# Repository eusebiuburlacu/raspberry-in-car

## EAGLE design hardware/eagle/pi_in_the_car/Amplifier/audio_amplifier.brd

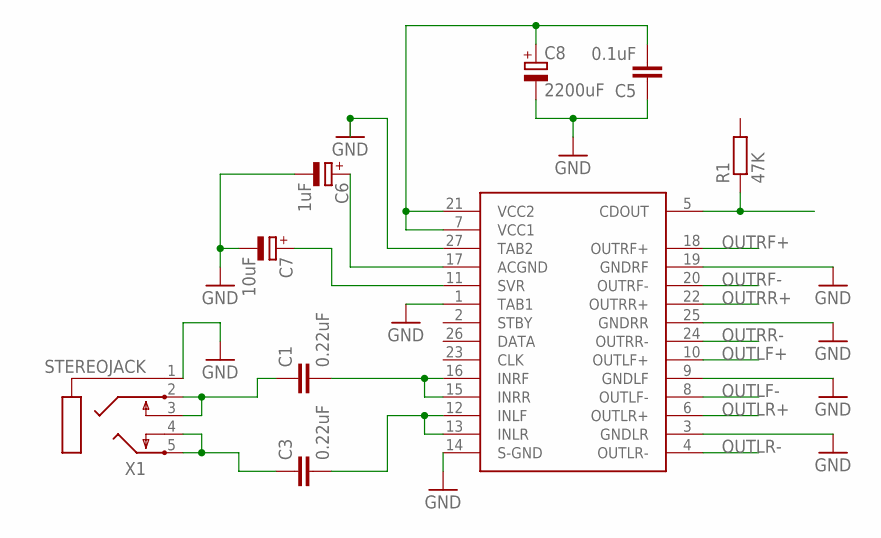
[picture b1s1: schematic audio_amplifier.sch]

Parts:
C1, C3: 0.22uF; C025-024X044
C5: 0.1uF; C025-024X044
C6: 1uF; 085CS_1AR
C7: 10uF; 085CS_1AR
C8: 2200uF; 085CS_1AR
R1: 47K; 0204/5
TDA7563A: TDA7563A; TDA7563
X1: STEREOJACK; STX3100

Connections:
GND: C5.1, C6.-, C7.-, C8.-, TDA7563A.1 (TAB1), TDA7563A.3 (GNDLR), TDA7563A.9 (GNDLF), TDA7563A.14 (S-GND), TDA7563A.19 (GNDRF), TDA7563A.25 (GNDRR), TDA7563A.27 (TAB2), X1.1
unnamed: C5.2, C8.+, TDA7563A.7 (VCC1), TDA7563A.21 (VCC2)
unnamed: C7.+, TDA7563A.11 (SVR)
unnamed: C6.+, TDA7563A.17 (ACGND)
unnamed: C1.2, TDA7563A.15 (INRR), TDA7563A.16 (INRF)
unnamed: C1.1, X1.2, X1.3
unnamed: C3.1, X1.4, X1.5
unnamed: C3.2, TDA7563A.12 (INLF), TDA7563A.13 (INLR)
unnamed: R1.1, TDA7563A.5 (CDOUT)
OUTLF+: TDA7563A.10 (OUTLF+)
OUTLF-: TDA7563A.8 (OUTLF-)
OUTLR+: TDA7563A.6 (OUTLR+)
OUTLR-: TDA7563A.4 (OUTLR-)
OUTRF+: TDA7563A.18 (OUTRF+)
OUTRF-: TDA7563A.20 (OUTRF-)
OUTRR+: TDA7563A.22 (OUTRR+)
OUTRR-: TDA7563A.24 (OUTRR-)

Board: 2 copper layers, 9 parts (0 on the bottom side), 9 nets, no tracks yet.

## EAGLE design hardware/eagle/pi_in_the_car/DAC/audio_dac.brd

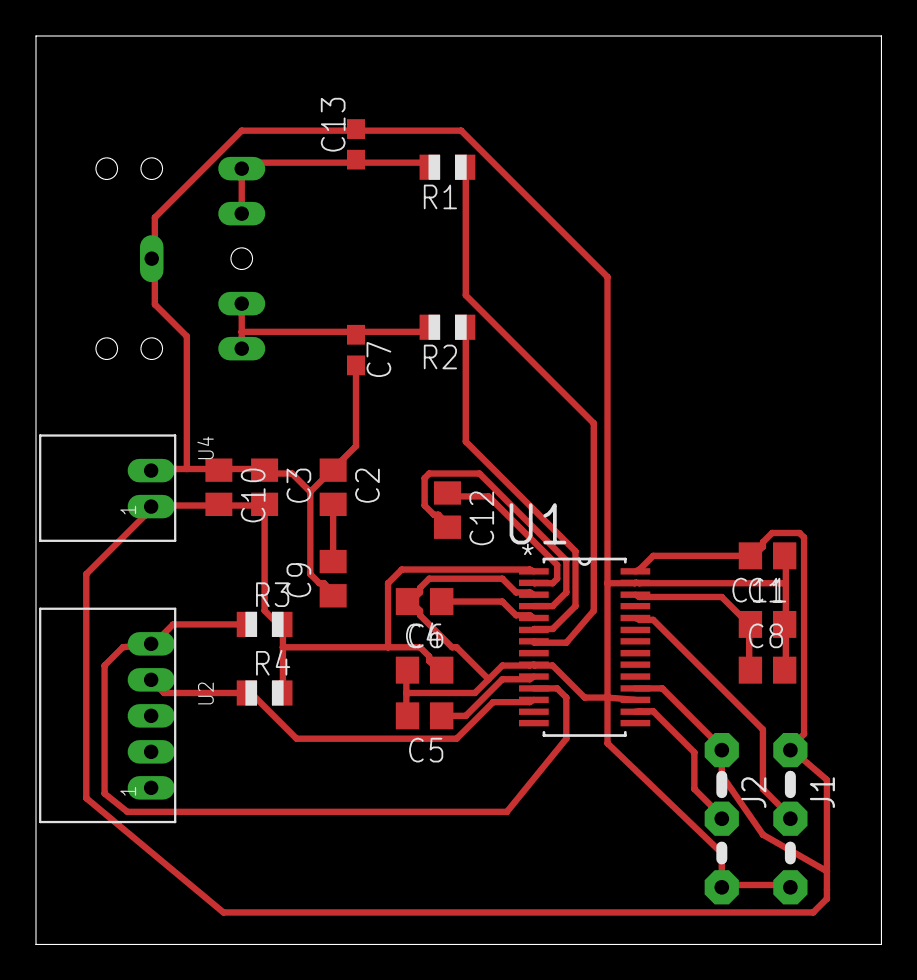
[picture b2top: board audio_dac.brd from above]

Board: 2 copper layers, 47.0 x 50.5 mm, 23 parts (1 on the bottom side), 19 nets.

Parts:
C1, C2, C3, C4, C5: 10uF; C0805
C6: 2.2uF; C0805
C7: 2.2uF; C0603
C8, C9, C10, C11: 0.1uF; C0805
C12: 2.2nF; C0805
C13: 2.2nF; C0603
J1, J2: 04C
R1, R2: 470R; R0805
R3, R4: 10k; R0805
U1: PCM5122PW; SOP65P640X120-28N
U2: I2S AND I2C; JST_B5B-PH_HEADER
U4: PWR; JST_B2B-PH_HEADER
U$1: FC68131; FC68131-5P

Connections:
3.3V: C2.2, C9.2
ADDR1: J1.2, U1.24
ADDR2: J2.2, U1.16
BCK: U1.21, U2.P3
DIN: U1.22, U2.P1
GND: C1.2, C2.1, C3.1, C4.1, C5.2, C6.2, C7.2, C8.2, C9.1, C10.1, C11.1, C13.2, J1.3, J2.3, U1.3, U1.9, U1.17, U1.27, U4.P2, U$1.1
LRCK: U1.23, U2.P2
unnamed: C1.1, C8.1, U1.26
unnamed: C12.2, U1.4
unnamed: C6.1, U1.5
unnamed: C12.1, U1.2
unnamed: C13.1, R1.2, U$1.2, U$1.3
unnamed: C7.1, R2.2, U$1.4, U$1.5
OUTL: R2.1, U1.6
OUTR: R1.1, U1.7
SCL: R4.1, U1.12, U2.P4
SDA: R3.1, U1.11, U2.P5
VCC: C3.2, C4.2, C10.2, C11.2, J1.1, J2.1, R3.2, R4.2, U1.1, U1.8, U1.18, U1.28, U4.P1
VCOM: C5.1, U1.10

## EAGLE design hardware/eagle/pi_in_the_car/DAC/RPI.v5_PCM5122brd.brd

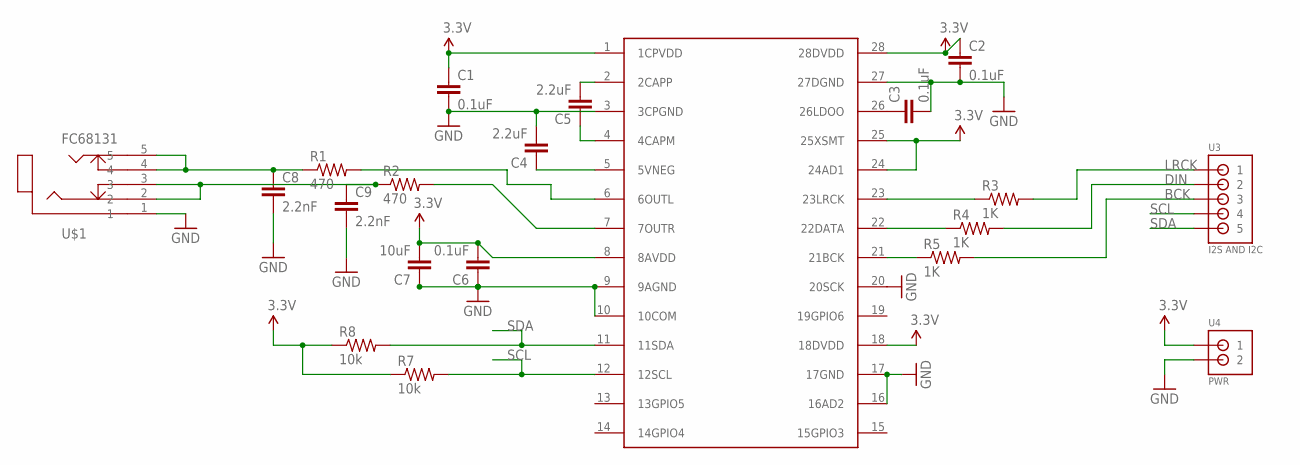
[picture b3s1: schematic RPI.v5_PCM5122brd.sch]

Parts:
C1, C2, C3, C6: 0.1uF; 0805
C4, C5: 2.2uF; 0805
C7: 10uF; 0805
C8, C9: 2.2nF; CAP-PTH-5MM
R1, R2: 470; AXIAL-0.4
R3, R4, R5: 1K; 0805
R7, R8: 10k; 1206
U3: I2S AND I2C; JST_B5B-PH_HEADER
U4: PWR; JST_B2B-PH_HEADER
U$1: FC68131; FC68131-5P
U$5: PCM5122; TSSOP28

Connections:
3.3V: C1.1, C2.1, C6.2, C7.2, R7.1, R8.1, U4.P1 (1), U$5.1 (1CPVDD), U$5.8 (8AVDD), U$5.18 (18DVDD), U$5.24 (24AD1), U$5.25 (25XSMT), U$5.28 (28DVDD)
BCK: R5.2, U3.P3 (3)
DIN: R4.2, U3.P2 (2)
GND: C1.2, C2.2, C3.2, C4.2, C6.1, C7.1, C8.2, C9.2, U4.P2 (2), U$1.1, U$5.3 (3CPGND), U$5.9 (9AGND), U$5.10 (10COM), U$5.16 (16AD2), U$5.17 (17GND), U$5.20 (20SCK), U$5.27 (27DGND)
LRCK: R3.2, U3.P1 (1)
unnamed: C3.1, U$5.26 (26LDOO)
unnamed: C5.2, U$5.2 (2CAPP)
unnamed: C5.1, U$5.4 (4CAPM)
unnamed: C4.1, U$5.5 (5VNEG)
unnamed: C9.1, R2.P$1 (1), U$1.2, U$1.3
unnamed: C8.1, R1.P$1 (1), U$1.4, U$1.5
unnamed: R1.P$2 (2), U$5.6 (6OUTL)
unnamed: R2.P$2 (2), U$5.7 (7OUTR)
unnamed: R3.1, U$5.23 (23LRCK)
unnamed: R4.1, U$5.22 (22DATA)
unnamed: R5.1, U$5.21 (21BCK)
SCL: R7.2, U3.P4 (4), U$5.12 (12SCL)
SDA: R8.2, U3.P5 (5), U$5.11 (11SDA)

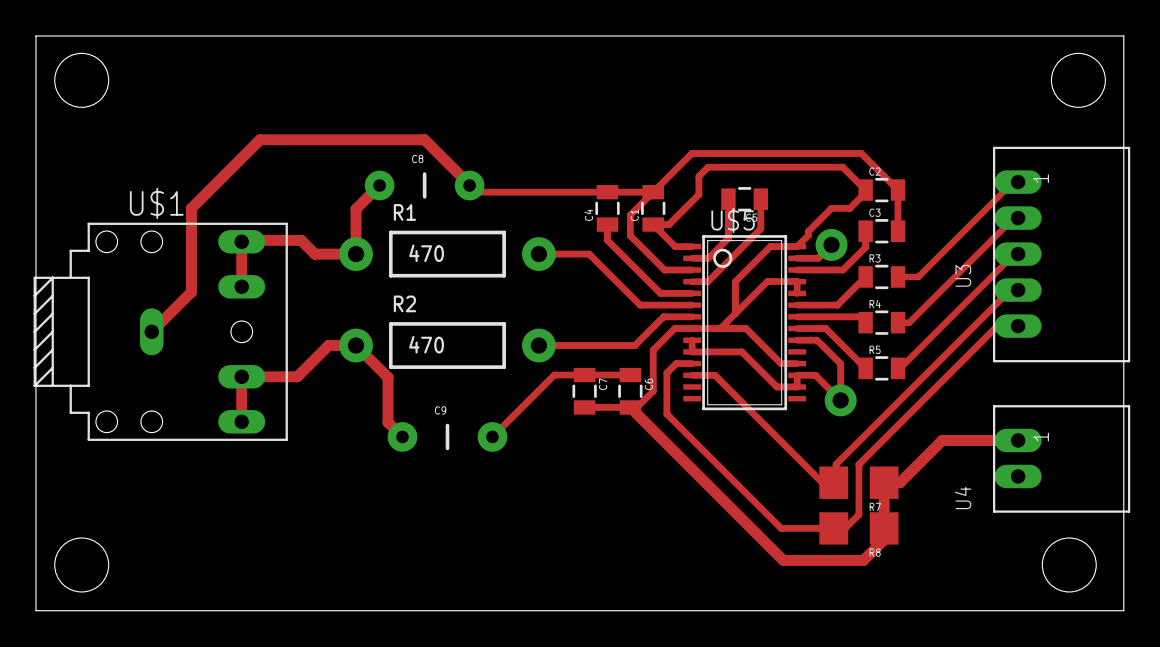
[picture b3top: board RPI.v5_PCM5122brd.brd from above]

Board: 2 copper layers, 60.4 x 31.9 mm, 20 parts (0 on the bottom side), 18 nets.

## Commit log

2018-09-16 Add initial sources of gui app
2018-09-16 Add hardware files
2018-09-16 Remove not needed hw files

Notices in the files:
parts and their libraries:
SparkFun-Capacitors: Licensing: CC v3.0 Share-Alike You are welcome to use this library for commercial purposes.
